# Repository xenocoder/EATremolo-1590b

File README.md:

EA Tremolo circuit on board to fit well in 1590b enclosure. Used the general Guitar Gadgets circuit.

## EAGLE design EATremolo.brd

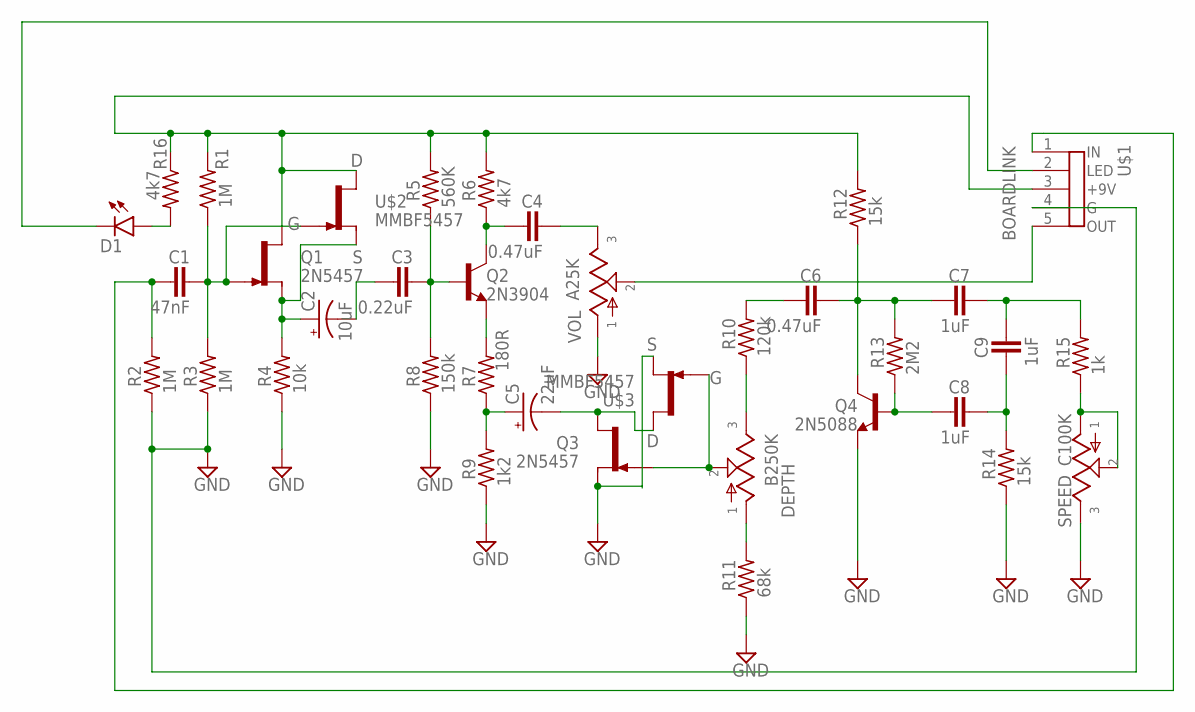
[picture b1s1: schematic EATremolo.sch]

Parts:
C1: 47nF; 072X025
C2: 10uF; 050_020_1
C3: 0.22uF; 072X035
C4, C6: 0.47uF; 072X035
C5: 22uF; 050_020_1
C7, C8, C9: 1uF; 072X045
D1: LED3MM
DEPTH: B250K; 16MM
Q1, Q3: 2N5457; TO92-
Q2: 2N3904; TO92-
Q4: 2N5088; TO92-
R1, R2, R3: 1M; R0207/3
R4: 10k; R0207/3
R5: 560K; R0207/3
R6, R16: 4k7; R0207/3
R7: 180R; R0207/3
R8: 150k; R0207/3
R9: 1k2; R0207/3
R10: 120k; R0207/3
R11: 68k; R0207/3
R12, R14: 15k; R0207/3
R13: 2M2; R0207/3
R15: 1k; R0207/3
SPEED: C100K; 16MM
U$1: BOARDLINK
U$2, U$3: MMBF5457; SOT23
VOL: A25K; 16MM

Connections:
GND: Q3.2 (S), Q4.3 (E), R2.1, R3.1, R4.1, R8.1, R9.1, R11.1, R14.1, SPEED.3, U$1.4 (G), U$3.2 (S), VOL.1
unnamed: C5.+, R7.1, R9.2
unnamed: C1.2, Q1.1 (G), R1.1, R3.2, U$2.3 (G)
unnamed: D1.A, R16.2
unnamed: C2.+, Q1.2 (S), R4.2, U$2.2 (S)
unnamed: C4.1, Q2.1 (C), R6.1
unnamed: C2.-, C3.1
unnamed: C3.2, Q2.2 (B), R5.1, R8.2
unnamed: Q2.3 (E), R7.2
unnamed: C5.-, Q3.3 (D), U$3.1 (D)
unnamed: C4.2, VOL.3
unnamed: DEPTH.2, Q3.1 (G), U$3.3 (G)
unnamed: DEPTH.3, R10.1
unnamed: DEPTH.1, R11.2
unnamed: C6.1, R10.2
unnamed: C6.2, C7.1, Q4.1 (C), R12.1, R13.2
unnamed: C8.1, Q4.2 (B), R13.1
unnamed: C7.2, C9.2, R15.2
unnamed: C8.2, C9.1, R14.2
unnamed: R15.1, SPEED.1, SPEED.2
unnamed: D1.K (C), U$1.2 (LED)
unnamed: U$1.5 (OUT), VOL.2
unnamed: Q1.3 (D), R1.2, R5.2, R6.2, R12.2, R16.1, U$1.3 (+9V), U$2.1 (D)
unnamed: C1.1, R2.2, U$1.1 (IN)

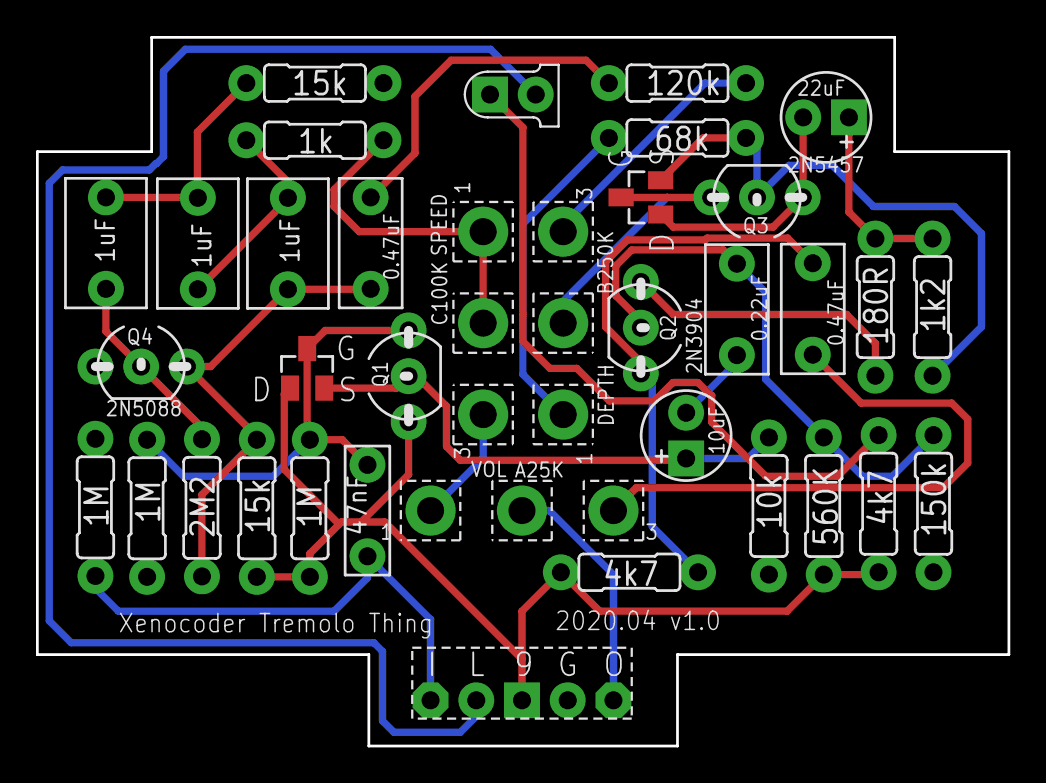
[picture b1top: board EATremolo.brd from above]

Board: 2 copper layers, 54.0 x 39.4 mm, 36 parts (0 on the bottom side), 24 nets.

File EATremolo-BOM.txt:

Partlist

Exported from EATremolo.brd at 4/28/20 9:11 PM

EAGLE Version 9.5.2 Copyright (c) 1988-2019 Autodesk, Inc.

Assembly variant: 

Part     Value          Package   Library         Position (mil)        Orientation

C1       47nF           072X025   mb_caps-box     (722 515)             R90
C2       10uF           050_020_1 mb_caps-electro (1419 679)            R90
C3       0.22uF         072X035   mb_caps-box     (1530 955)            R90
C4       0.47uF         072X035   mb_caps-box     (1696 956)            R270
C5       22uF           050_020_1 mb_caps-electro (1725 1375)           R180
C6       0.47uF         072X035   mb_caps-box     (729 1100)            R270
C7       1uF            072X045   mb_caps-box     (548 1099)            R90
C8       1uF            072X045   mb_caps-box     (150 1100)            R90
C9       1uF            072X045   mb_caps-box     (351 1099)            R270
D1       LED3MM         LED3MM    mb_diodes       (1040 1425)           R0
DEPTH    B250K          16MM      mb_pots         (1150 925)            R270
Q1       2N5457         TO92-     mb_trans        (812 809)             R90
Q2       2N3904         TO92-     mb_trans        (1320 915)            R270
Q3       2N5457         TO92-     mb_trans        (1574 1200)           R180
Q4       2N5088         TO92-     mb_trans        (227 830)             R0
R1       1M             R0207/3   mb_resistors    (596 520)             R270
R2       1M             R0207/3   mb_resistors    (127 522)             R270
R3       1M             R0207/3   mb_resistors    (240 520)             R90
R4       10k            R0207/3   mb_resistors    (1600 525)            R90
R5       560K           R0207/3   mb_resistors    (1720 525)            R270
R6       4k7            R0207/3   mb_resistors    (1295 380)            R180
R7       180R           R0207/3   mb_resistors    (1833 960)            R270
R8       150k           R0207/3   mb_resistors    (1960 530)            R90
R9       1k2            R0207/3   mb_resistors    (1958 960)            R90
R10      120k           R0207/3   mb_resistors    (1400 1450)           R180
R11      68k            R0207/3   mb_resistors    (1400 1330)           R180
R12      15k            R0207/3   mb_resistors    (480 520)             R270
R13      2M2            R0207/3   mb_resistors    (360 521)             R270
R14      15k            R0207/3   mb_resistors    (607 1450)            R180
R15      1k             R0207/3   mb_resistors    (607 1325)            R180
R16      4k7            R0207/3   mb_resistors    (1840 530)            R90
SPEED    C100K          16MM      mb_pots         (975 925)             R90
U$1      BOARDLINK      BOARDLINK xc_library      (960 100)             R0
U$2      MMBF5457       SOT23     xc_library      (590 826)             R0
U$3      MMBF5457       SOT23     xc_library      (1320 1200)           R90
VOL      A25K           16MM      mb_pots         (1060 515)            R180

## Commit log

2015-10-08 Files for v1.0
2018-10-19 Added Schematic and BOM
2018-10-21 Fixed issue where speed pot was wired (and laid out) backwards
2018-11-17 Updated MMBF5457 to right footprint
2018-11-24 Fixed issue with SMD 5457
2020-04-29 Version 1.0 of Tremolo Thing
2020-04-29 Deleted backup files
2025-11-22 Adds Affinity design and CAM files
